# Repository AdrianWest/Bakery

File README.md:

<p align="center">
  <strong>If Bakery has helped you in any way please consider buying me a coffee</strong>
</p>

<p align="center">
<table align="center">
  <tr>
    <td align="center">
      
    </td>
    <td align="center">
      
    </td>
  </tr>
</table>
</p>

# Bakery - KiCad Plugin

**Localize all KiCad symbols, footprints, 3D models, and datasheets to project libraries - They get Baked into your project**

---

## ⚠️ **IMPORTANT: Protect Your Design** ⚠️

### **This plugin makes extensive changes to your schematic and PCB files.**

### **Bakery creates a KiCad-compatible ZIP backup before it changes your project.**

**Why?**
- Bakery modifies `.kicad_sch` and `.kicad_pcb` files extensively
- Bakery now supports restoring a previous design with KiCad's built-in **Unarchive Project** command
- Each backup is saved as `<project>-backups/<project>-YYYY-MM-DD_HHMMSS.zip`
- Version control is still recommended for complete history and day-to-day change tracking

**Recommended: put your project under Git before running Bakery:**
```bash
cd /path/to/your/project
git init
git add .
git commit -m "Before Bakery localization"
```

---

## Overview

Bakery is a KiCad plugin that automates the process of copying global library symbols, footprints, 3D models, and datasheets into project-local libraries. The plugin **"bakes in"** all external dependencies, converting references from global libraries to local project files. This ensures:
- **Project portability**: No external library dependencies - everything is baked into your project
- **Version stability**: Libraries won't change if global libraries are updated
- **Self-contained projects**: All files and dependencies are contained in the project folder
- **Complete independence**: Share projects without worrying about missing libraries

## Installation

### Option 1: Via KiCad Plugin Manager (Recommended)

1. Open KiCad
2. Go to **Tools** > **Plugin and Content Manager**
3. Search for "Bakery"
4. Click **Install**

### Option 2: Install from ZIP File

1. Download the latest release ZIP from [GitHub Releases](https://github.com/AdrianWest/Bakery/releases)
2. In KiCad, go to **Tools** > **Plugin and Content Manager**
3. Click **Install from File...**
4. Select the downloaded `Bakery-x.x.x.zip` file
5. Click **Open** to install

### Option 3: Manual Installation

1. Download or clone this repository
2. Copy the `plugins` folder contents to your KiCad plugins directory:
   - **Windows**: `%USERPROFILE%\Documents\KiCad\10.0\scripting\plugins\Bakery\`
   - **Linux**: `~/.kicad/10.0/scripting/plugins/Bakery/`
   - **Linux (Flatpak)**: `~/.var/app/org.kicad.KiCad/data/kicad/10.0/scripting/plugins/Bakery/`
   - **macOS**: `~/Library/Preferences/kicad/10.0/scripting/plugins/Bakery/`

   > **Note (Flatpak):** KiCad installed via Flatpak runs in a sandbox and
   > does not see `~/.kicad/...`. Copy the plugin into the sandboxed data
   > directory shown above, or KiCad will not detect it. After copying,
   > fully quit KiCad (not just close the window) before relaunching so it
   > rescans the plugins folder.
3. Restart KiCad

> **Note:** Bakery currently supports **KiCad 10.x only**. If you are still
> on KiCad 9.x (including Flatpak builds), use the last 9.x-compatible
> release, [v1.1.0](https://github.com/AdrianWest/Bakery/releases/tag/v1.1.0),
> instead of the current release.

### Uninstalling on Windows

For a manual installation, close KiCad and run `uninstall.bat` from this
repository. It removes `%USERPROFILE%\Documents\KiCad\10.0\scripting\plugins\Bakery`.
Use `uninstall.bat /NonInteractive` (or `/Q`) to skip the final pause.
Project libraries and backups are preserved. For installations managed by
KiCad's **Plugin and Content Manager**, uninstall Bakery through that manager.

## How To Use Bakery

### 1. Prepare Your Project

1. Save your KiCad project, schematic, and PCB.
2. Close any other KiCad windows that have the project open.
3. Confirm that the project is under version control if possible. Bakery also
   creates a timestamped KiCad ZIP backup before making changes.

### 2. Run Bakery

1. Open the project's PCB in **PCB Editor**.
2. Click the  icon in the
   top toolbar, or select **Tools** > **External Plugins** >
   **Bakery - Localize Symbols, Footprints, and 3d Models**.
3. Choose the local library and folder names in the configuration dialog.
4. Confirm the operation and leave KiCad open while Bakery completes.

### Configuration Dialog Fields

These names control the project-local libraries and folders Bakery creates.
The defaults are safe for most projects; change them only if you want different
names in your KiCad project folder.

| Field | What to enter | What Bakery creates or updates |
|-------|---------------|--------------------------------|
| **Local Footprint Library Name** | A KiCad library nickname, such as `MyLib` | A local footprint library folder named `MyLib.pretty` and an `fp-lib-table` entry for it |
| **Symbol Library Name** | A KiCad symbol library nickname, such as `MySymbols` | A local symbol library file named `MySymbols.kicad_sym` and a `sym-lib-table` entry for it |
| **Symbol Directory Name** | A folder name, such as `MySym` or `Symbols` | The folder that stores the local symbol library file |
| **3D Models Directory Name** | A folder name, such as `3D Models` | The folder that stores copied STEP/WRL model files |
| **Datasheets Directory Name** | A folder name, such as `Data_Sheets` | The folder that stores downloaded or copied PDF datasheets |
| **Place all library folders inside one folder** | Check to group the output folders | Places the footprint, symbol, 3D model, and datasheet folders inside a single folder in the project |
| **Parent Folder Name** | A folder name (default: `Project_Lib`); shown when grouping is checked | The parent folder containing all the library folders |

Click **OK** to start localization, **Cancel** to exit without changes, or
**Help** to open the Bakery GitHub repository.

Bakery will:
   - Create `<project>-backups/<project>-YYYY-MM-DD_HHMMSS.zip`
   - Create local `.pretty` folders for footprints
   - Create local symbol library (`.kicad_sym`) in Symbols directory
   - Create local `3D Models` folder for 3D models
   - Create local `Data_Sheets` folder for datasheets
   - Copy all used symbols, footprints, and their associated 3D models
   - Download datasheets from internet URLs and copy local datasheet files into the project datasheet folder
   - Scan and localize datasheet references from both schematic and PCB files
   - Update `fp-lib-table` and `sym-lib-table` to include local libraries
   - Update references in both PCB and schematic files to point to local libraries
   - Abort before making changes if the project backup cannot be created

### 3. Check the Result

1. Review Bakery's log, warnings, and errors before closing KiCad.
2. Open the schematic and PCB to confirm that symbols and footprints load
   correctly.
3. Open the 3D Viewer to confirm copied 3D models render as expected.
4. The project is now portable: its localized libraries, models, and
   datasheets are stored in the project folder.

## Restore a Previous Design

Bakery backups are standard KiCad ZIP project archives. Restore a previous
design at any time with KiCad's built-in **Unarchive Project** command:

1. Close the current project.
2. In the KiCad Project Manager, select **File** > **Unarchive Project...**.
3. Select the desired ZIP from the project's `<project>-backups` folder.
4. Select a new, empty folder for the restored project. Do not restore over
   the current design until you have confirmed the backup is correct.
5. Open the restored `.kicad_pro` file and verify the schematic and PCB.
6. If it is correct, replace the current project only if needed.

For details, see the official KiCad documentation:
[Project archive and unarchive](https://docs.kicad.org/10.0/en/kicad/kicad.html#project-archive).

## Project Structure After Localization

```
YourProject/
├── YourProject.kicad_pro
├── YourProject.kicad_pcb
├── YourProject.kicad_sch
├── YourProject-backups/      # Timestamped pre-localization project archives
│   └── YourProject-YYYY-MM-DD_HHMMSS.zip
├── fp-lib-table              # Updated with local footprint library
├── sym-lib-table             # Updated with local symbol library
├── MyLib.pretty/             # Local footprint library
│   ├── Footprint1.kicad_mod
│   └── Footprint2.kicad_mod
├── Symbols/                  # Local symbol libraries
│   └── MySymbols.kicad_sym  # Local symbol library
├── 3D Models/                # Local 3D models
│   ├── model1.step
│   └── model2.wrl
└── Data_Sheets/              # Local datasheets
    ├── component1.pdf
    └── component2.pdf
```

## Development

See [.github/copilot-instructions.md](.github/copilot-instructions.md) for development guidelines and architecture details.

### Project Architecture

```
Bakery/
├── __init__.py                 # Plugin registration and metadata
├── bakery_plugin.py            # Main plugin class (ActionPlugin interface)
├── constants.py                # Configuration constants and messages
├── ui_components.py            # Logger window and configuration dialog
├── footprint_localizer.py      # Footprint and 3D model localization
├── symbol_localizer.py         # Symbol localization
├── data_sheet_localizer.py     # Datasheet localization (download/copy/update)
├── library_manager.py          # Footprint library table management
├── sexpr_parser.py             # S-expression parser
├── utils.py                    # Shared utility functions
└── metadata.json               # Plugin metadata for KiCad Plugin Manager
```

## Features

   ✅ **Symbol Localization**: Automatically copies all symbols from global libraries to your project
   
   ✅ **Footprint Localization**: Automatically copies all footprints from global libraries to your project

   ✅ **3D Model Localization**: Copies associated 3D models and updates paths

   ✅ **Datasheet Localization**: Downloads datasheets from internet URLs or copies local PDF files to your project; updates all references to use portable `${KIPRJMOD}` paths

   ✅ **Automatic Reference Updates**: Updates PCB, schematics, and library tables

   ✅ **Dual Scanning**: Scans both PCB and schematic files for complete coverage

   ✅ **Automatic Project Backup**: Creates a KiCad-compatible timestamped ZIP before changing project files

   ✅ **Progress Tracking**: Visual progress bar with step-by-step status

   ✅ **Detailed Logging**: Separate panes for info, warnings, and errors

   ✅ **Configurable**: Choose local library and directory names

   ✅ **Path Safety**: Validates all file operations to prevent data loss

   ✅ **KiCad 10 Support**: Built for KiCad version 10

## Requirements

- KiCad 10.x
- Python 3.x (bundled with KiCad)
- wxPython (bundled with KiCad)

## Configuration

When you run Bakery, you can configure:
- **Local Footprint Library Name**: Name for the local footprint library (default: "MyLib")
- **Symbol Library Name**: Name for the local symbol library file (default: "MySymbols")
- **Symbol Directory Name**: Name for the symbol library directory (default: "Symbols")
- **3D Models Folder**: Name for the 3D models folder (default: "3D Models")
- **Datasheets Directory Name**: Name for the local datasheets folder (default: "Data_Sheets")
- **Automatic Project Backup**: Mandatory and created in `<project>-backups`

## License

GNU General Public License v3.0 - see LICENSE file

## Contributing

Contributions welcome! Please open an issue or pull request.

Please note that this project is released with a [Code of Conduct](CODE_OF_CONDUCT.md). By participating in this project you agree to abide by its terms.

## Roadmap

### Version 2.2.0 - Current Release

- [x] Optional grouping of library folders inside a named parent folder (default: `Project_Lib`)
- [x] KiCad 10 project support, including projects that still reference 9.x global libraries
- [x] Localization of symbols, footprints, 3D models, and datasheets into project-local libraries
- [x] Collision-safe local names and filenames for symbols, footprints, 3D models, and datasheets
- [x] Mandatory KiCad-compatible, timestamped ZIP backup before localization
- [x] Restore previous designs through KiCad's **File** > **Unarchive Project...** command
- [x] Safe repeat runs that preserve local `${KIPRJMOD}` 3D model paths
- [x] Detection and user-visible warnings for unresolved local symbol references
- [x] Recursive hierarchical-schematic processing and dual PCB/schematic scanning
- [x] Automated unit tests and Windows KiCad 10 functional tests that reopen both the localized PCB and root schematic

### Planned for Future Versions

- [ ] KiCad 11 compatibility review and support
- [ ] Additional localization and recovery improvements based on user feedback
- [ ] Expanded functional-test coverage for new KiCad versions and project configurations

## Testing

### Unit Tests

The unit suite uses Python's built-in `unittest` framework and mocks the
KiCad APIs where necessary. From the repository root:

```powershell
python "Unit Test\run_tests.py"             # Run all unit tests
python "Unit Test\run_tests.py" --verbose   # Show each test name
python "Unit Test\run_tests.py" --list      # List discovered test modules
python "Unit Test\run_tests.py" --coverage  # Write terminal and HTML coverage reports
```

`--coverage` requires the optional `coverage` package:

```powershell
python -m pip install coverage
```

The suite covers the plugin entry point, localization modules, backup and
configuration handling, utilities, library management, and S-expression
parsing. See [Unit Test/README.md](Unit%20Test/README.md) for test-specific
details.

### Automated Functional Tests

The functional suite drives a real **KiCad 10** installation through its UI.
It restores all four fixture projects, installs the plugin, runs Bakery,
checks the localized project files, verifies a second run makes no unintended
changes, and reopens the localized PCB and root schematic in KiCad.

**Requirements**

- Windows with KiCad 10 installed
- Python 3.x
- `pywinauto`, `pywin32`, and `psutil`
- No open `pcbnew.exe` or Bakery plugin process

Install the Python test dependencies once:

```powershell
python -m pip install pywinauto pywin32 psutil
```

From the repository root, run the complete suite or selected fixtures:

```powershell
# Run FT-01 through FT-04
python "Functional Test\functional_suite\run_functional_tests.py"

# Run only selected fixtures while iterating
python "Functional Test\functional_suite\run_functional_tests.py" --fixtures FT-01,FT-03

# Run one localization pass only, without the second-run or PCB/schematic reopen checks
python "Functional Test\functional_suite\run_functional_tests.py" --skip-idempotence --skip-reopen
```

Test workspace files are created under `C:\GIT_HUB\testing`. Each run writes
`junit.xml`, `summary.json`, `environment.json`, and `report.md` to
`C:\GIT_HUB\testing\results\<timestamp>\`. Datasheet download failures and
the fixtures' deliberately missing references are asserted as expected
conditions; unexpected localization, PCB reopen, or schematic reopen failures
cause a nonzero exit code.

See [Functional Test/functional_suite/README.md](Functional%20Test/functional_suite/README.md)
for the fixture matrix, assertions, expected issues, and report details.

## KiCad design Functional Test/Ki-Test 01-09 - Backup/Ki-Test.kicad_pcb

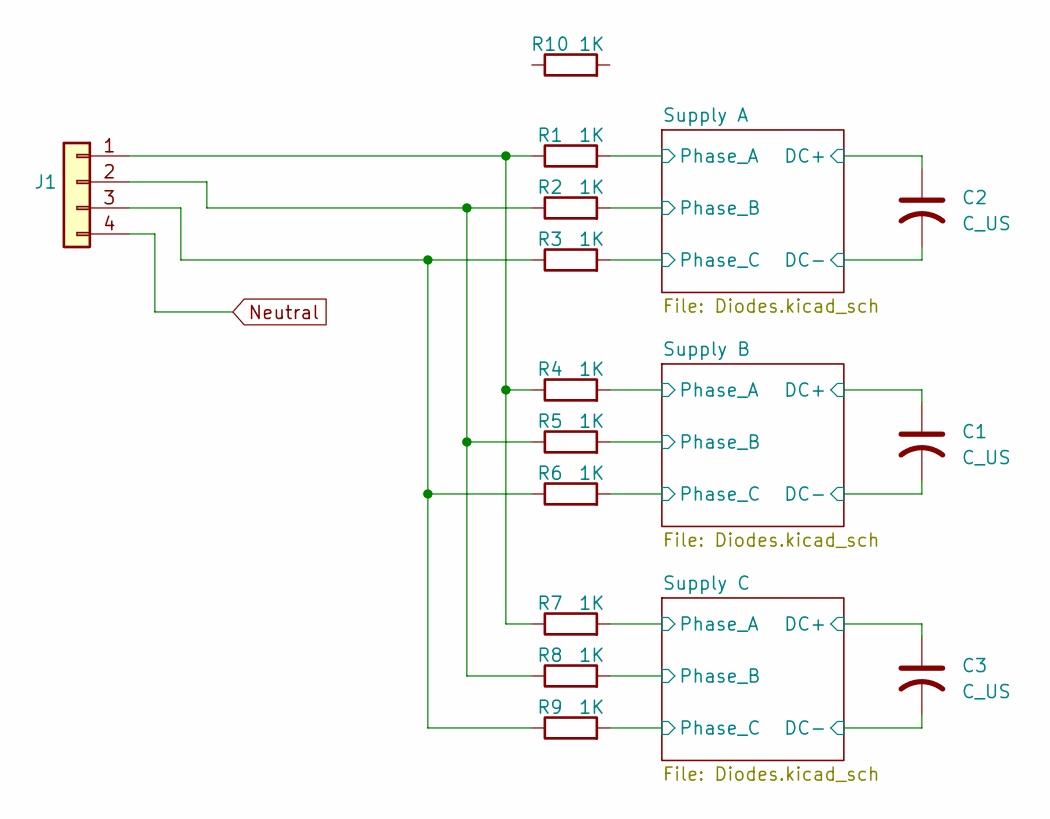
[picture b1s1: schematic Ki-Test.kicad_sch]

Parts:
C1, C2, C3: C_US; CP_Elec_18x22
J1: Conn_01x01
R1, R2, R3, R4, R5, R6, R7, R8, R9, R10: 1K; R_4020_10251Metric_Pad1.65x5.30mm_HandSolder

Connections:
/Supply A/Phase_A: R1.2; also elsewhere on the board
/Supply A/Phase_B: R2.2; also elsewhere on the board
/Supply A/Phase_C: R3.2; also elsewhere on the board
/Supply B/Phase_A: R4.2; also elsewhere on the board
/Supply B/Phase_B: R5.2; also elsewhere on the board
/Supply B/Phase_C: R6.2; also elsewhere on the board
/Supply C/Phase_A: R7.2; also elsewhere on the board
/Supply C/Phase_B: R8.2; also elsewhere on the board
/Supply C/Phase_C: R9.2; also elsewhere on the board
GND: C1.2, C2.2, C3.2; also elsewhere on the board
unnamed: J1.1, R1.1, R4.1, R7.1
unnamed: J1.2, R2.1, R5.1, R8.1
unnamed: J1.3, R3.1, R6.1, R9.1
Neutral: J1.4
VBUS: C1.1, C2.1, C3.1; also elsewhere on the board

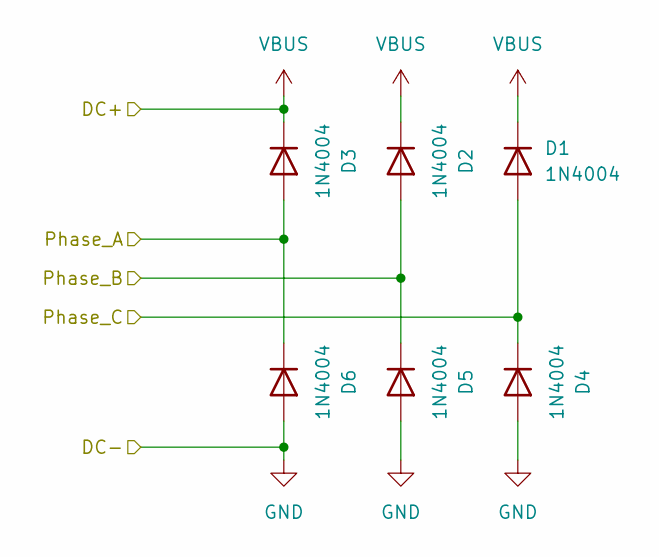
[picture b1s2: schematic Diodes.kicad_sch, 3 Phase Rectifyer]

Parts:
D1, D2, D3, D4, D5, D6: 1N4004; D_DO-41_SOD81_P10.16mm_Horizontal

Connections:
/Supply B/Phase_A: D3.2 (A), D6.1 (K); also elsewhere on the board
/Supply B/Phase_B: D2.2 (A), D5.1 (K); also elsewhere on the board
/Supply B/Phase_C: D1.2 (A), D4.1 (K); also elsewhere on the board
GND: D4.2 (A), D5.2 (A), D6.2 (A); also elsewhere on the board
VBUS: D1.1 (K), D2.1 (K), D3.1 (K); also elsewhere on the board

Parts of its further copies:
D7, D8, D9, D10, D11, D12, D13, D14, D15, D16, D17, D18: 1N4004; D_DO-41_SOD81_P10.16mm_Horizontal

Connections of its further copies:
/Supply A/Phase_A: D7.2 (A), D8.1 (K); also elsewhere on the board
/Supply A/Phase_B: D9.2 (A), D10.1 (K); also elsewhere on the board
/Supply A/Phase_C: D11.2 (A), D12.1 (K); also elsewhere on the board
/Supply C/Phase_A: D13.2 (A), D14.1 (K); also elsewhere on the board
/Supply C/Phase_B: D15.2 (A), D16.1 (K); also elsewhere on the board
/Supply C/Phase_C: D17.2 (A), D18.1 (K); also elsewhere on the board
GND: D8.2 (A), D10.2 (A), D12.2 (A), D14.2 (A), D16.2 (A), D18.2 (A); also elsewhere on the board
VBUS: D7.1 (K), D9.1 (K), D11.1 (K), D13.1 (K), D15.1 (K), D17.1 (K); also elsewhere on the board

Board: 2 copper layers, 31 parts (0 on the bottom side), 14 nets, no tracks yet.

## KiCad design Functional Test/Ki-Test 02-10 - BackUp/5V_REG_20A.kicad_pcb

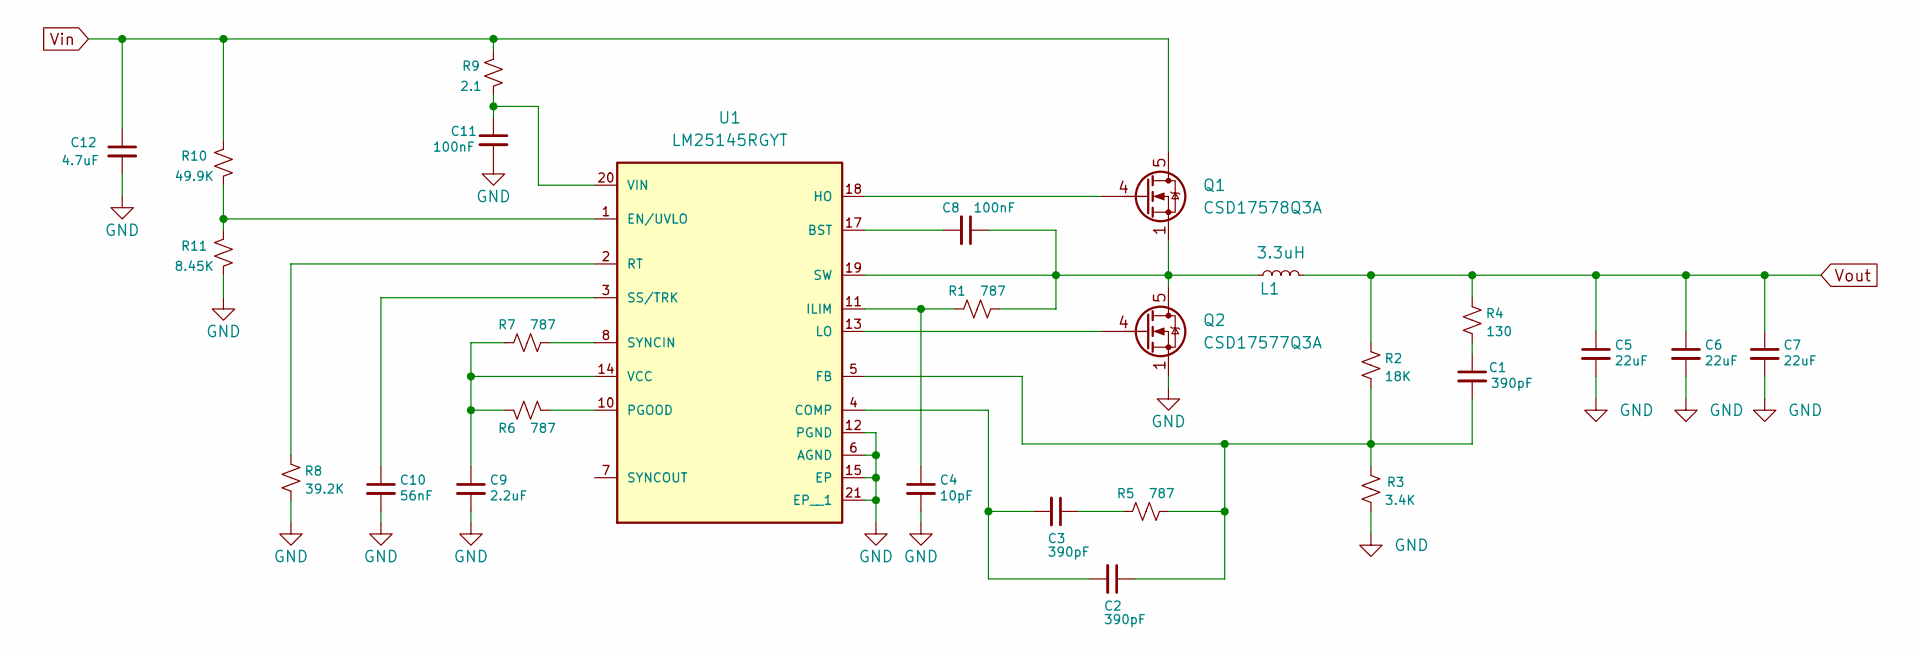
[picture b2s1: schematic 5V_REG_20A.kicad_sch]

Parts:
C1: 390pF; C_0402_1005Metric; Manufacturer Part No GRM155R71H391KA01D
C2: 390pF; C_0402_1005Metric; Manufacturer Part No GRM155R71C102KA01D
C3: 390pF; C_0402_1005Metric; Manufacturer Part No GRM155R71C822KA01D
C4: 10pF; C_0603_1608Metric; Manufacturer Part No GRM1885C2A100JA01D
C5, C6, C7: 22uF; C_1210_3225Metric; Manufacturer Part No MCASL32MSB5226MPNA01
C8, C11: 100nF; C_0603_1608Metric; Manufacturer Part No CGA3E2X7R1H104K080AA
C9: 2.2uF; C_1206_3216Metric; Manufacturer Part No CGA5L2X7R1E225K160AA
C10: 56nF; C_0402_1005Metric; Manufacturer Part No GRM155R71C563KA88D
C12: 4.7uF; C_1210_3225Metric; Manufacturer Part No MSASU32MSB7475MPNA01
L1: 3.3uH; IND_XAL7070_COC-M; Manufacturer Part No XAL7070-332MEC
Q1: CSD17578Q3A; 8-PowerVDFN; Manufacturer Part No CSD17578Q3A
Q2: CSD17577Q3A; 8-PowerVDFN; Manufacturer Part No CSD17577Q3A
R1: 787; R_0402_1005Metric; Manufacturer Part No CRCW0402787RFKED
R2: 18K; R_0603_1608Metric; Manufacturer Part No RC0603FR-0718KL
R3: 3.4K; R_0402_1005Metric; Manufacturer Part No CRCW04023K40FKED
R4: 130; R_0402_1005Metric; Manufacturer Part No CRCW0402130RFKED
R5: 787; R_0402_1005Metric; Manufacturer Part No CRCW04021K47FKED
R6, R7: 787; R_0603_1608Metric; Manufacturer Part No RC0603FR-0720KL
R8: 39.2K; R_0402_1005Metric; Manufacturer Part No CRCW040239K2FKED
R9: 2.1; R_0603_1608Metric; Manufacturer Part No CRCW06032R10FKEA
R10: 49.9K; R_0402_1005Metric; Manufacturer Part No CRCW040249K9FKED
R11: 8.45K; R_0603_1608Metric; Manufacturer Part No RC0603FR-078K45L
U1: LM25145RGYT; QFN50P350X450X100-20N; Manufacturer Part No LM25145RGYR

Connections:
GND: C4.2, C5.2, C6.2, C7.2, C9.2, C10.2, C11.2, C12.2, Q2.1 (S), R3.1, R8.1, R11.1, U1.6 (AGND), U1.12 (PGND), U1.15 (EP), U1.21 (EP__1)
unnamed: C1.1, R4.1
unnamed: C3.1, R5.1
unnamed: Q1.4 (G), U1.18 (HO)
unnamed: C8.1, L1.1, Q1.1 (S), Q2.5 (D), R1.2, U1.19 (SW)
unnamed: Q2.4 (G), U1.13 (LO)
unnamed: C8.2, U1.17 (BST)
unnamed: C2.2, C3.2, U1.4 (COMP)
unnamed: R10.1, R11.2, U1.1 (EN/UVLO)
unnamed: C1.2, C2.1, R2.1, R3.2, R5.2, U1.5 (FB)
unnamed: C4.1, R1.1, U1.11 (ILIM)
unnamed: R6.2, U1.10 (PGOOD)
unnamed: R8.2, U1.2 (RT)
unnamed: C10.1, U1.3 (SS/TRK)
unnamed: R7.2, U1.8 (SYNCIN)
unnamed: C9.1, R6.1, R7.1, U1.14 (VCC)
unnamed: C11.1, R9.1, U1.20 (VIN)
Vin: C12.1, Q1.5 (D), R9.2, R10.2
Vout: C5.1, C6.1, C7.1, L1.2, R2.2, R4.2

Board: 2 copper layers, 27 parts (0 on the bottom side), 19 nets, no tracks yet.

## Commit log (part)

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2026-01-13 First time pushing in
    This has bugs, I was unable to revert because I did not set up a repo. I have learned my lesion.
2026-01-13 Update Licesnse and gett an Icon in KiCad
2026-01-14 Bug fixes and compile errors
2026-01-14 all run time issues resolved, now we need to do some testing
2026-01-14 updated IConsa and figured out the best size, updated change log and documents
2026-01-15 general clean up
2026-01-15 code clean up and a 'im done' windo
2026-01-15 hierarchical schematics are untested
2026-01-15 Added code of conduct
2026-01-18 Bug fix - symbols not infile if ther was no file to start with.
2026-01-18 localizer methods now inharit from a base
2026-01-18 Added untest and functional tests
2026-01-18 update documentation
2026-01-18 fixed code review feed back
2026-01-19 Moving things around for the release to the plug in repo
2026-01-19 getting ready to release the code
2026-01-19 remove zip file
2026-01-19 Trying to release
2026-01-19 Ok im going to try to build the release properly
2026-01-19 removed old zip file
2026-01-19 building a release batch file
2026-01-19 Update metadata for v1.0.0 release
2026-01-19 still refining the replease process
2026-01-19 I think I have it sorted out now
2026-01-19 Found a damb bug when Iwas trying to release. The icon now registers with the new folder structure
2026-01-19 Release v1.0.0 - Updated metadata with package hash and sizes
2026-01-19 Release v1.0.1 - Updated metadata with package hash and sizes
2026-01-19 metea data is messed up
2026-01-19 still struggling to make a kiCad compliant release
2026-01-19 updated change log
2026-01-19 updated release notes
2026-01-20 bug fixes for the release script and folder orgnazation to meet the kiCad stndard
2026-01-20 correcting the releas processing of the json files
2026-01-20 updated release script
2026-01-20 Release tool tested and works
2026-01-20 corrected and added icons
2026-01-27 updated build script for the repo
2026-02-22 Start version 1.1.0 - Adding datasheet copy and icon features
2026-02-22 Add resources folder with icons
2026-02-22 Update create_release.bat to include root-level resources folder
2026-02-22 Update CHANGELOG.md with resources folder changes
2026-02-22 Update README overview to emphasize 'bakes in' concept
2026-02-22 Update installation instructions with Plugin Manager and install from ZIP options
2026-02-22 Update usage instructions to mention Bakery icon button in toolbar
2026-02-22 Replace Bakery text with icon image in usage instructions
2026-02-22 Update CHANGELOG with README documentation improvements
2026-02-22 Add data_sheet_localizer.py skeleton for datasheet localization feature
2026-02-22 Update data_sheet_localizer to focus on symbols (datasheets are in symbols, not footprints)
2026-02-22 Add datasheets directory name configuration option to GUI (default: Data_Sheets)
2026-02-22 Update CHANGELOG with detailed datasheet localizer implementation
2026-02-22 Add deduplication logic to datasheet localizer to avoid copying duplicates
2026-02-22 Clarify datasheet localizer handles both internet URLs and local file paths
2026-02-22 Add PDF-only filtering to datasheet localizer - skip non-PDF datasheets
2026-02-22 Update CHANGELOG with PDF-only filtering and URL download details
2026-02-22 Add date comparison logic to keep latest version when datasheet file exists
2026-02-22 Add comprehensive logging requirements for all datasheet operations
2026-02-22 Add update_schematic_references method to replace datasheet values in schematic files
2026-02-22 Implement update_symbol_references to replace datasheet URLs in symbol libraries
2026-02-22 Update CHANGELOG with complete datasheet localization implementation details
2026-02-22 Clarify completion message to show datasheet count more explicitly
2026-02-22 Track and report separate counts for internet downloads vs local file copies
2026-02-22 Implement full datasheet localization: scanning, downloading, copying, and reference updating
2026-02-22 Consolidate repetitive code: extract PDF validation and file comparison helpers
2026-02-22 Integrate datasheet localization into main plugin workflow
2026-02-22 Update CHANGELOG.md with code consolidation and workflow integration changes
2026-02-22 Fix ZIP filename format: use underscores (x_y_z) instead of dots while keeping version as x.y.z in JSON
2026-02-22 Add data_sheet_localizer.py to release package file list
2026-02-22 Add data_sheet_localizer.py to install.bat file list
2026-02-24 Add datasheet localization, unit tests, documentation, and bug fixes
    - Add data_sheet_localizer.py: scan, download, copy, and update PDF datasheets
    - Fix S-expression parser quote handling for property name matching
    - Fix safe_read_file error handling for missing files
    - Add Unit Test/test_data_sheet_localizer.py: 74 tests for DataSheetLocalizer
    - Update Unit Test/run_tests.py: add cgi stub for Python 3.13+ compatibility
    - Update Unit Test/TESTING_GUIDE.md: add test_data_sheet_localizer.py entry
2026-02-24 Update Read Me
2026-02-27 Needed to fix a folder issue the git lab scripts do not like \
2026-03-28 fix: add KiCad 10 compatibility
    Two issues prevented the plugin from loading in KiCad 10:
    1. metadata.json had kicad_version_max set to 9.99, which tells
    KiCad's PCM to reject the plugin for KiCad 10+. Removed the
    upper bound so the plugin is available in KiCad 10.
    2. __init__.py used inspect.stack() to check for LoadPluginModule
    in the call stack before registering. This brittle check fails
